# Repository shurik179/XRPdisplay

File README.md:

# XRP display
This project describes a small TFT display designed for use  with [XRP robot](https://experientialrobotics.org/)

## Features

* 135x240 TFT SPI display
* two user buttons
* two addressable RGB LEDs (Neopixels)
* Power switch

## Documentation 
Detailed documentation is available at https://xrpdisplay.readthedocs.io/

## License
Everything in this repository is available under MIT license, except for the fonts in software/lib. See README file in that folder for license information.

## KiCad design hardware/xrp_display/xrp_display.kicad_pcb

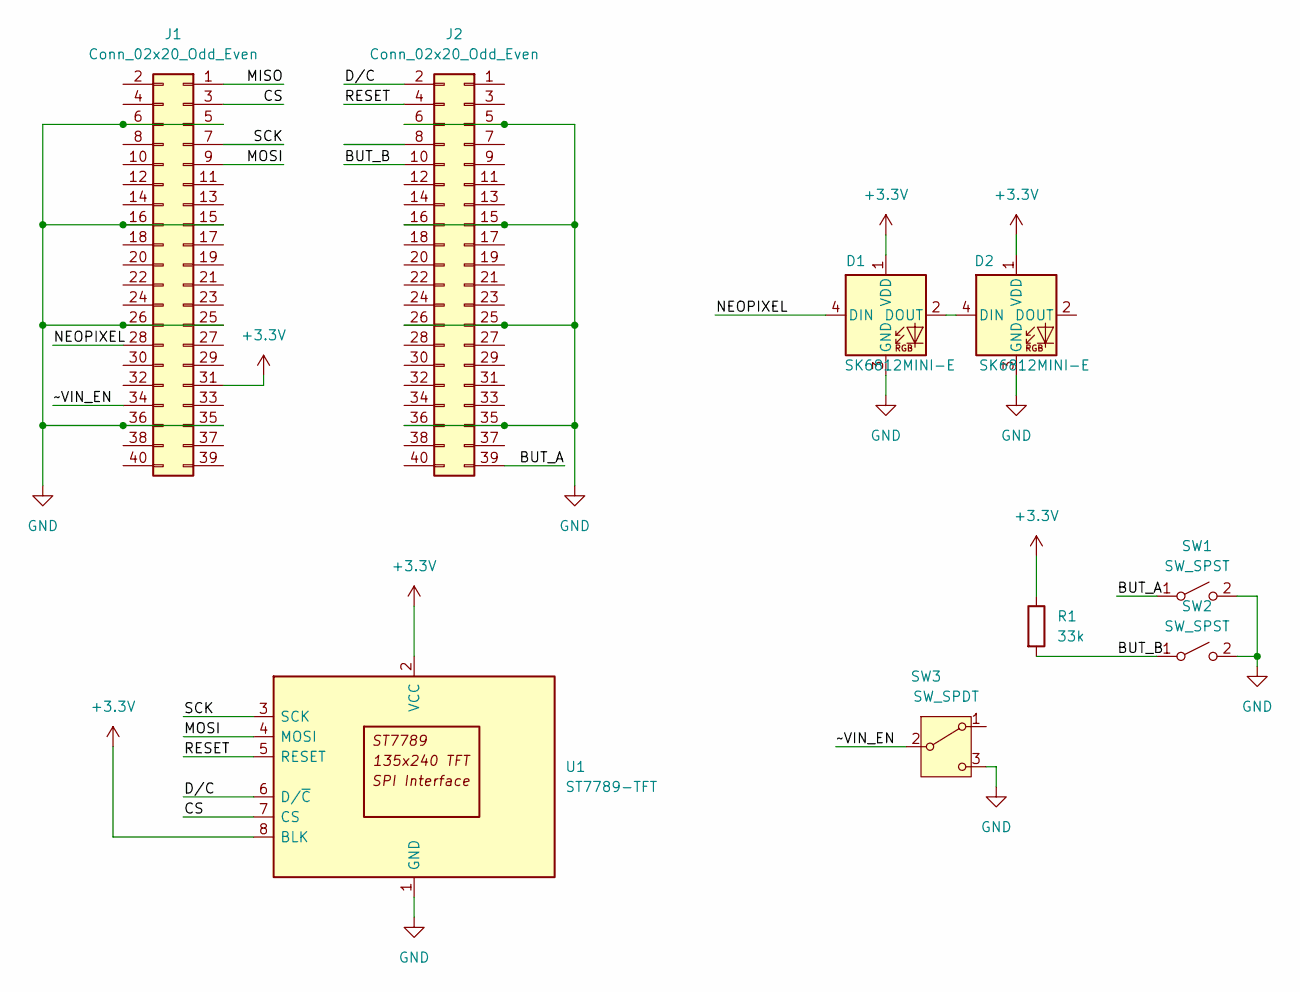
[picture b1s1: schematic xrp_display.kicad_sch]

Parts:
D1, D2: SK6812MINI-E; SK6812-MINI-E; LCSC C5149201
J1, J2: Conn_02x20_Odd_Even; PinHeader_2x20_P2.54mm_Vertical_SMD; LCSC C6332245
R1: 33k; R_0603_1608Metric
SW1, SW2: SW_SPST; SW_TH_Tactile_Omron_B3F-10xx
SW3: SW_SPDT; SW_XKB_SS12D10L3
U1: ST7789-TFT; TFT_135x240_1_14in

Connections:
+3.3V: D1.1 (VDD), D2.1 (VDD), J1.31, R1.1, U1.2 (VCC), U1.8 (BLK)
/BUT_A: J2.39, SW1.1 (A)
/BUT_B: J2.10, R1.2, SW2.1 (A)
/CS: J1.3, U1.7 (CS)
/D/C: J2.2, U1.6 (D/~C)
/MISO: J1.1
/MOSI: J1.9, U1.4 (MOSI)
/NEOPIXEL: D1.4 (DIN), J1.28
/RESET: J2.4, U1.5 (RESET)
/SCK: J1.7, U1.3 (SCK)
/~VIN_EN: J1.34, SW3.2 (B)
GND: D1.3 (GND), D2.3 (GND), J1.5, J1.6, J1.15, J1.16, J1.25, J1.26, J1.35, J1.36, J2.5, J2.6, J2.15, J2.16, J2.25, J2.26, J2.35, J2.36, SW1.2 (B), SW2.2 (B), SW3.3 (C), U1.1 (GND)
unnamed: D1.2 (DOUT), D2.4 (DIN)

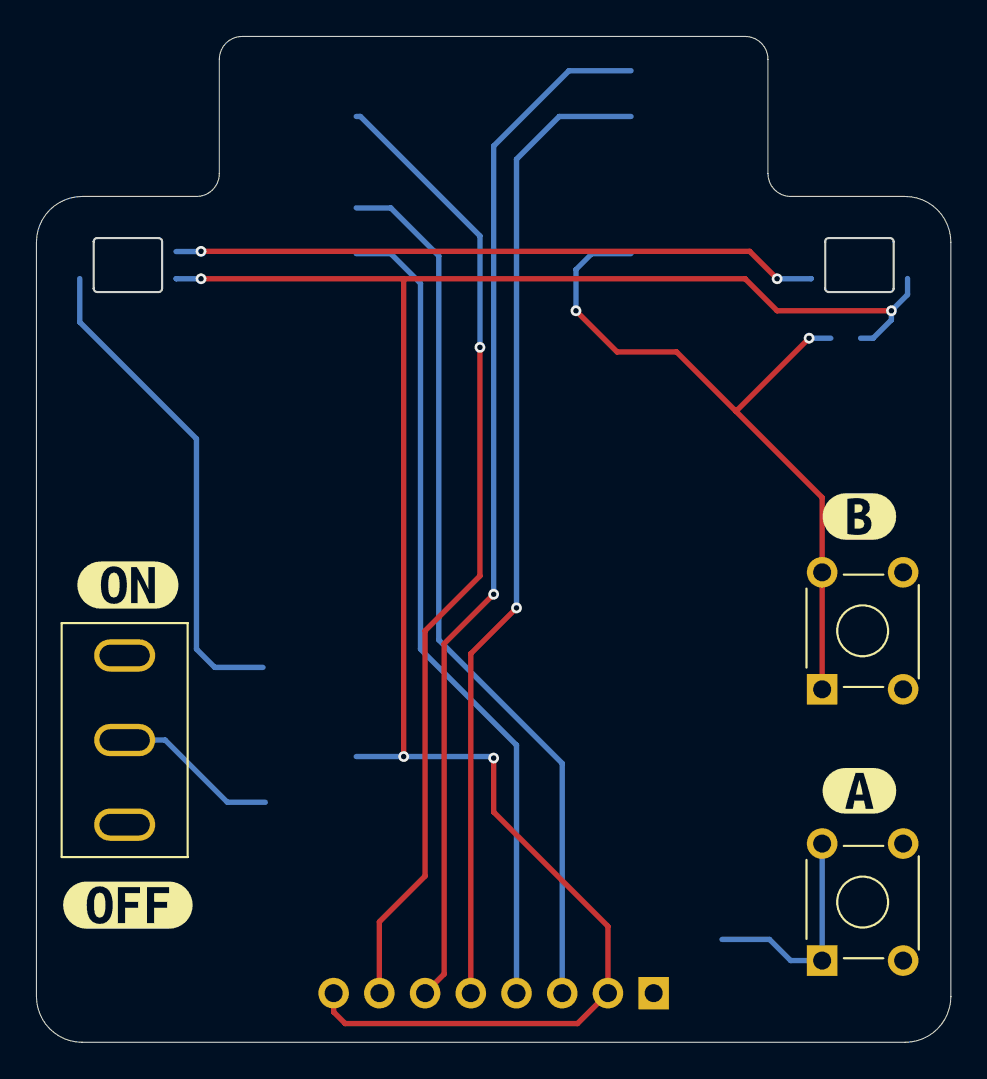
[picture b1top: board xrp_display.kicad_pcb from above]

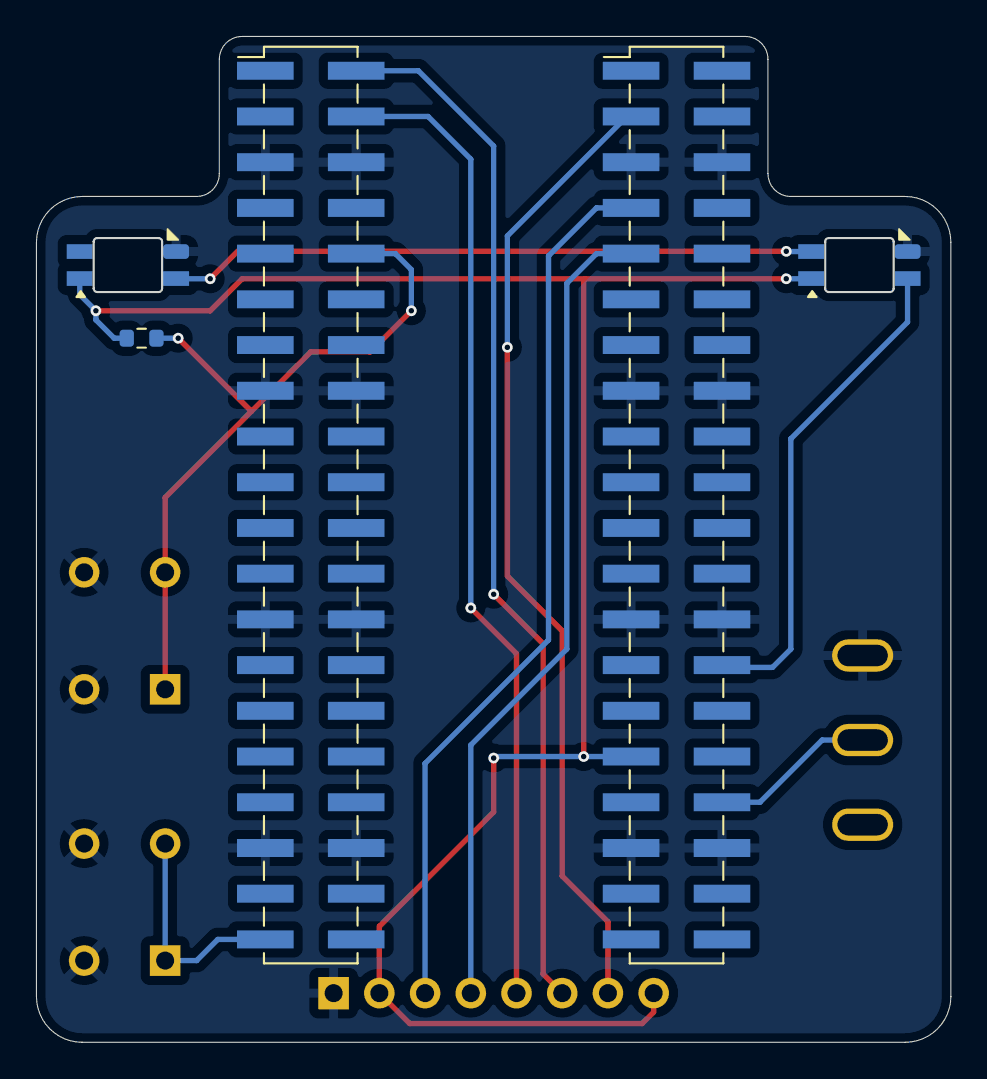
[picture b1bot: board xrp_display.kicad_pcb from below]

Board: 2 copper layers, 50.7 x 55.8 mm, 13 parts (5 on the bottom side), 12 nets.

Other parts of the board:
kibuzzard-67F032A5: G***; kibuzzard-67F032A5
kibuzzard-67F0329B: G***; kibuzzard-67F0329B
kibuzzard-67F03336: G***; kibuzzard-67F03336
kibuzzard-67F03342: G***; kibuzzard-67F03342

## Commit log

2025-04-28 created README
2025-04-28 initial upload
2025-04-28 added 3d printed support
2025-04-28 docs update
2025-04-29 added license info for software
2025-04-30 Added battery voltage
